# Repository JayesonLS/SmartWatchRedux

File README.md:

SmartWatch Redux
================

Modern replacements for the DS1216 SmartWatch variants.

SmartWatchRedux-E
-----------------

Status: Version 1.0 built, tested and working. Version 1.1 (minor changes) untested.

A replacement for the DS1216-E. This SmartWatch is for use on a BIOS
or exapansion ROM socket. It is typically placed in between an existing
BIOS ROM and its socket.

This clock is compatible with Y2K and current dates when used with this
software availalbe here: https://www.dropbox.com/s/kctqpwzjxgymfz9/smwy2k.zip?dl=0
or here: 
ftp://ftp.oldskool.org/pub/tvdog/tandy1000/utilities/smwy2k.zip

ATD-20-Redux
------------

Status: Untested. 

A replacement for the ATD-20 clock. This is used in ATD exansion boards 
for the Tandy 1000 computers such as the T512CLK-A1. It is believed that
the ATD-20 is, or is compatible with, the DS1216-B/C SmartWatch. However, 
the ATD-20 does not allow, nor require, a BIOS rom to be fitted to the 
top of the module.

A DS1216-C has been tested in a T512CLK-A1 and works fine. If purchasing
an original DS1216-C today, it may be necessary to retrofit a battery replacement.
Google "DS1216 battery replacement". 

Software for the ATD-20 (or DS1216-C) located in a T512CLK-A1 is available
from here: http://www.minuszerodegrees.net/rtc/rtc.htm . It seems to work
correctly with current dates.

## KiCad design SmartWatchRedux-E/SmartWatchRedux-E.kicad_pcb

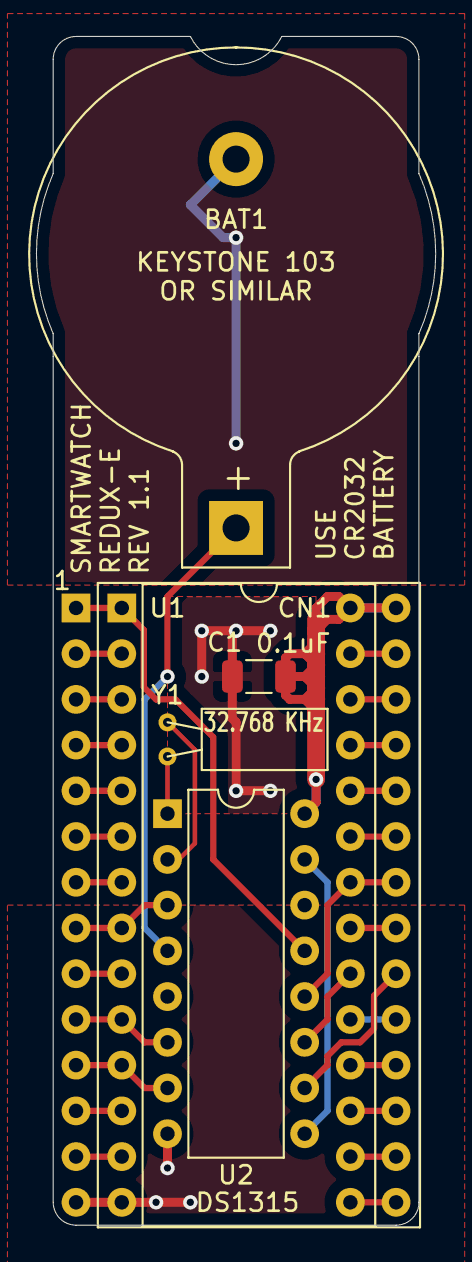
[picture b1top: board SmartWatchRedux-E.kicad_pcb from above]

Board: 2 copper layers, 22.2 x 66.0 mm, 6 parts (0 on the bottom side), 33 nets.

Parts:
BAT1: CR2032; BatteryHolder_Keystone_103_1x20mm
C1: 0.1uF; C_1206_3216Metric
CN1: 27C256Socket; DIP-28_W15.24mm
U1: ROM; DIP-28_W15.24mm_Socket
U2: DS1315; DIP-16_W7.62mm
Y1: 32.768 KHz; Crystal_C38-LF_D3.0mm_L8.0mm_Horizontal

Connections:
/XTAL1: U2.1, Y1.1
/XTAL2: U2.2, Y1.2
GND: BAT1.2, C1.2, CN1.14, U1.14, U2.5, U2.8, U2.14
unnamed: BAT1.1, U2.4
unnamed: CN1.1, U1.1, U2.13
unnamed: CN1.2, U1.2
unnamed: CN1.3, U1.3
unnamed: CN1.4, U1.4
unnamed: CN1.5, U1.5
unnamed: CN1.6, U1.6
unnamed: CN1.7, U1.7
unnamed: CN1.8, U1.8, U2.3
unnamed: CN1.9, U1.9
unnamed: CN1.10, U1.10, U2.6
unnamed: CN1.11, U1.11, U2.7
unnamed: CN1.12, U1.12
unnamed: CN1.13, U1.13
unnamed: CN1.15, U1.15
unnamed: CN1.16, U1.16
unnamed: CN1.17, U1.17
unnamed: CN1.18, U1.18
unnamed: CN1.19, U1.19
unnamed: CN1.20, U2.11
unnamed: CN1.21, U1.21
unnamed: CN1.22, U1.22, U2.12
unnamed: CN1.23, U1.23
unnamed: CN1.24, U1.24
unnamed: CN1.25, U1.25
unnamed: CN1.26, U1.26
unnamed: CN1.27, U1.27
unnamed: U1.20, U2.10
unnamed: U2.9, U2.15
VCC: C1.1, CN1.28, U1.28, U2.16

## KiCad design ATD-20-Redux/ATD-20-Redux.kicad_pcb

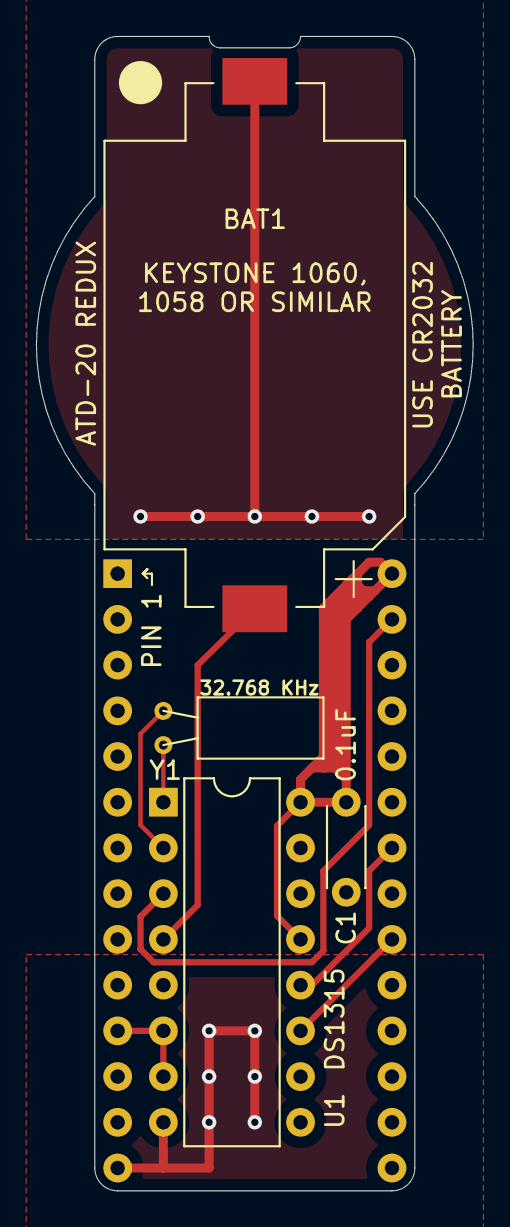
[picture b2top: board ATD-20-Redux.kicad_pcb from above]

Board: 2 copper layers, 24.3 x 64.1 mm, 5 parts (0 on the bottom side), 9 nets.

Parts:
BAT1: CR2032; BatteryHolder_Keystone_1060_1x2032
C1: 0.1uF; C_Disc_D4.3mm_W1.9mm_P5.00mm
J1: RTC Pins; DIP-28_W15.24mm_Socket
U1: DS1315; DIP-16_W7.62mm
Y1: 32.768 KHz; Crystal_C38-LF_D3.0mm_L8.0mm_Horizontal

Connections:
/D0: J1.11, U1.6, U1.7
/XTAL1: U1.1, Y1.1
/XTAL2: U1.2, Y1.2
/~CS_RTC: J1.20, U1.11
/~IOR: J1.22, U1.12
/~IOW: J1.27, U1.3
GND: BAT1.2, C1.2, J1.14, U1.5, U1.8, U1.9, U1.14
unnamed: BAT1.1, U1.4
VCC: C1.1, J1.28, U1.13, U1.16

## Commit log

2021-04-02 Strip non-SmartWatch projects from a copy of TandyCircuitsAndLogic in order to place SmartWatch projects into their own repository.
2021-04-02 Rename SmartWatchRedux to SmartWatchRedux-E.
2021-04-02 Update Readme.
2021-04-02 Minor tweakes to board, add -E to name.
2021-04-02 SmartWatchRedux-E: Fix version number.
2021-04-02 SmartWatchRedux-E: Add gerbers
2021-04-03 Flipped layout of ATD-20 Redux so battery was at other end. This is to make it easier to change the battery. The battery holder is also slightly off-center to allow battery holder pin to fit between 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
2021-04-04 Add files missing from previous commit.
2021-04-04 Add gerbers for AssembyBoard.
2021-04-04 Add initial pass at assembly board.
2021-04-04 Update SmartWatchRedux-E gerbers.
2021-04-04 Add gerbets for ATD-20-Redux.
2021-05-06 Minor tweaks to ATD-20-Redux.
2021-05-06 Change battery holder on ATD-20-Redux to something that is not as tall. This is to increase the distance between the battery and the adjacent board.
2021-05-06 Gerber plots for AssemblyBoard and SmartWatchRedux. Minor board shape change on SmartWatchRedux.
2021-05-06 Gerbers for ATD-20-Redux.
2021-05-18 ATD-20-Redux - Add small notch to indicate top of board.
2021-05-18 Create SmartWatchRedux-E-SMT: SMT version of SmartWatchRedux-E. Switches both the crystal and the battery holder to SMT. The bypass cap was already SMT.
2023-11-04 Adding SmartWatchTest which is dated from 2021-07-14. Not sure what kind of state this is in.

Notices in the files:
ATD-20-Redux/ATD-20-Redux.kicad_pcb:
into the public domain
